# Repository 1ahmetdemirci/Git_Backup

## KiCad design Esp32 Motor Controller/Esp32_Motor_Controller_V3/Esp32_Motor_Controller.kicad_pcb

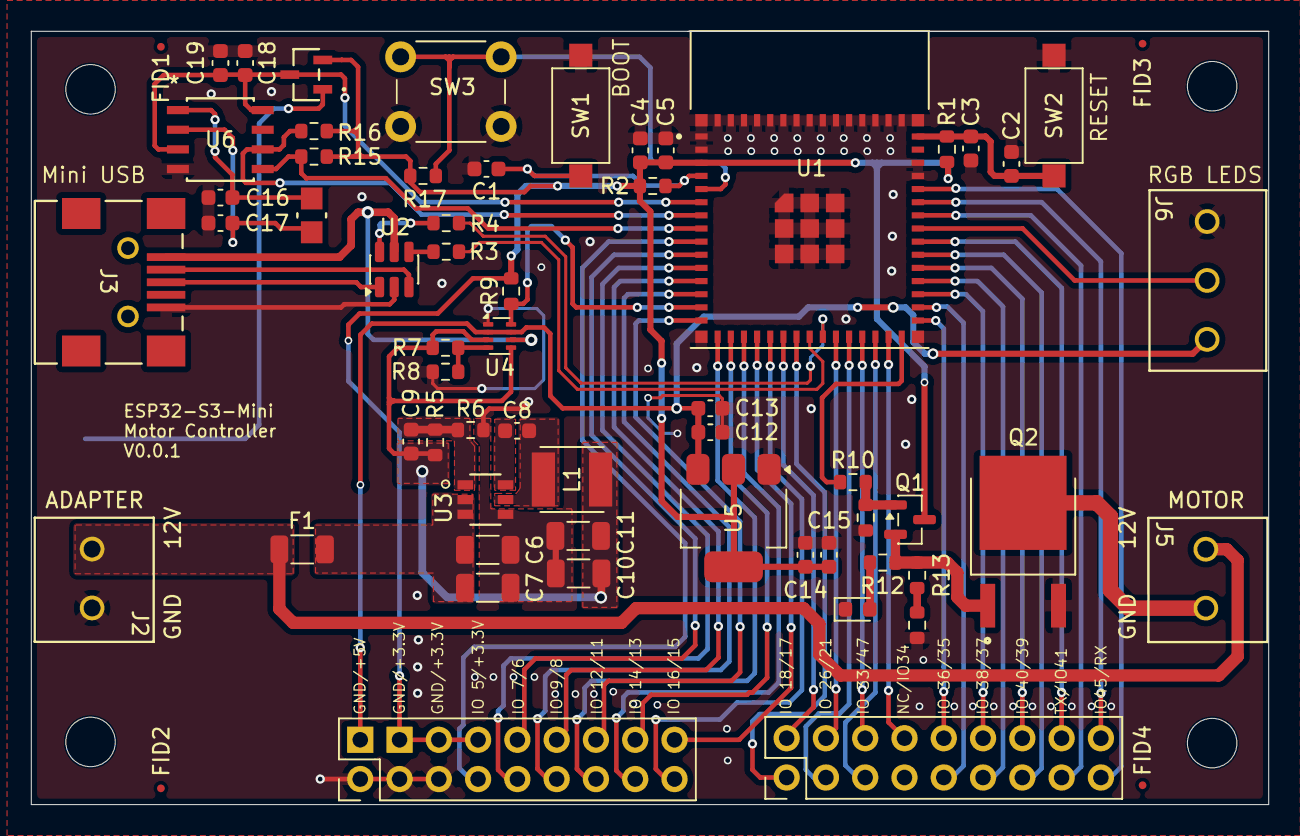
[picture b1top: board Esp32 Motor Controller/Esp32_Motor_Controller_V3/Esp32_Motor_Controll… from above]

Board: 2 copper layers, 80.0 x 50.0 mm, 63 parts (1 on the bottom side), 62 nets.

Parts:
BT2: BC2032-E2
C1, C2, C3, C4, C8, C13, C14, C18: 100nF_0603; C_0603_1608Metric
C5, C12, C15, C19: 10uF_0603; C_0603_1608Metric
C6: 10uF_1206; C_1206_3216Metric
C7: 100nF_1206; C_1206_3216Metric
C9: 47pF_0603; C_0603_1608Metric
C10, C11: 22uF_0603; C_1206_3216Metric
C16, C17: 12.5pF_0603; C_0603_1608Metric
CR1: BAT54C-TP; BAT54C-TP_MCE
D1: Green_Led; LED_0603_1608Metric
F1: C1F 2; C_1206_3216Metric
FID1, FID2, FID3, FID4: Fiducial; Fiducial_0.5mm_Mask1mm
J1, J7: Conn_02x09_Odd_Even; PinHeader_2x09_P2.54mm_Vertical
J2, J5: Screw_Terminal_01x02; 1x2_1727010
J3: USB_B_Mini; 690-005-299-043_EDA
J6: Screw_Terminal_01x03; 1x3_1727023
L1: 6.8uH; SRP4021HMCT-6R8M
Q1: MMBT2222A; SOT-23
Q2: MJD122T4G
R1, R2, R8, R9, R17: 10k_0603; R_0603_1608Metric
R3, R4: 22R_0603; R_0603_1608Metric
R5: 158k; R_0603_1608Metric
R6: 30k1; R_0603_1608Metric
R7: 33k_0603; R_0603_1608Metric
R10, R13, R15, R16: 4.7k_0603; R_0603_1608Metric
R11, R14: 47k_0603; R_0603_1608Metric
R12: 1k_0603; R_0603_1608Metric
SW1: BOOT; SW_SPST_CK_RS282G05A3
SW2: ESP_EN; SW_SPST_CK_RS282G05A3
SW3: BUTTON; SW_PUSH_6mm_H13mm
U1: ESP32-S3-MINI-1-N8
U2: USBLC6-2SC6; SOT-23-6
U3: AP63300WU-7; AP63301WU-7
U4: TPS2116DRL; SOT-583-8
U5: AMS1117-3.3; SOT-223-3_TabPin2
U6: PCF8563T/5_518; PCF8563T
XTAL1: RT3215-32.768-12.5-TR

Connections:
+3V3: C4.1, C5.1, C14.1, C15.1, CR1.2, J1.4, J1.6, J1.8, Q1.3 (C), R1.1, R2.1, R9.1, R15.1, R16.1, R17.1, U1.3 (3V3), U5.2 (VO)
+5V: C9.1, C10.1, C11.1, L1.2, R5.1, R7.2, U4.3 (VIN1), U4.5 (MODE)
+12V: F1.1, J2.1, J5.1
/ESP32_S3_Mini/ESP_D+: R4.2, U1.24 (IO20)
/ESP32_S3_Mini/ESP_D-: R3.2, U1.23 (IO19)
/ESP32_S3_Mini/LOAD: C12.1, C13.1, J1.2, J6.3, U4.2 (VOUT), U4.7 (VOUT), U5.3 (VI)
/ESP32_S3_Mini/Motor_Control: R10.1, U1.30 (IO48)
/ESP32_S3_Mini/Power Selection: R9.2, U1.14 (IO10), U4.8 (ST)
/ESP32_S3_Mini/RGB_Control: J6.2, U1.38 (IO42)
BOOT: C1.1, R2.2, SW1.2, U1.4 (IO0)
BUTTON: R17.2, SW3.2, U1.5 (IO1)
ESP_EN: C2.1, C3.2, R1.2, SW2.2, U1.45 (EN)
GND: BT2.N, C1.2, C2.2, C3.1, C4.2, C5.2, C6.2, C7.2, C10.2, C11.2, C12.2, C13.2, C14.2, C15.2, C16.2, C17.2, C18.1, C19.1, D1.1 (K), J1.1, J1.3, J1.5, J2.2, J3.5 (GND), J6.1, Q2.3, R6.2, R8.1, R11.1, R14.1, SW1.1, SW2.1, SW3.1, U1.1 (GND), U1.2 (GND), U1.42 (GND), U1.43 (GND), U1.46 (GND), U1.47 (GND), U1.48 (GND), U1.49 (GND), U1.50 (GND), U1.51 (GND), U1.52 (GND), U1.53 (GND), U1.54 (GND), U1.55 (GND), U1.56 (GND), U1.57 (GND), U1.58 (GND), U1.59 (GND), U1.60 (GND), U1.61 (GND), U1.61_1 (GND), U1.61_2 (GND), U1.61_3 (GND), U1.61_4 (GND), U1.61_5 (GND), U1.61_6 (GND), U1.61_7 (GND), U1.61_8 (GND), U1.62 (GND), U1.63 (GND), U1.64 (GND), U1.65 (GND), U2.2 (GND), U3.4 (GND), U4.1 (GND), U5.1 (GND), U6.4 (VSS)
IO5: J1.7, U1.9 (IO5)
IO6: J1.10, U1.10 (IO6)
IO7: J1.9, U1.11 (IO7)
IO8: J1.12, U1.12 (IO8)
IO9: J1.11, U1.13 (IO9)
IO11: J1.14, U1.15 (IO11)
IO12: J1.13, U1.16 (IO12)
IO13: J1.16, U1.17 (IO13)
IO14: J1.15, U1.18 (IO14)
IO15: J1.18, U1.19 (IO15)
IO16: J1.17, U1.20 (IO16)
IO17: J7.2, U1.21 (IO17)
IO18: J7.1, U1.22 (IO18)
IO21: J7.4, U1.25 (IO21)
IO26: J7.3, U1.26 (IO26)
IO33: J7.5, U1.28 (IO33)
IO34: J7.8, U1.29 (IO34)
IO35: J7.10, U1.31 (IO35)
IO36: J7.9, U1.32 (IO36)
IO37: J7.12, U1.33 (IO37)
IO38: J7.11, U1.34 (IO38)
IO39: J7.14, U1.35 (IO39)
IO40: J7.13, U1.36 (IO40)
IO41: J7.16, U1.37 (IO41)
IO45: J7.17, U1.41 (IO45)
IO47: J7.6, U1.27 (IO47)
unnamed: D1.2 (A), R12.1
unnamed: J3.3 (D+), U2.1 (I/O1)
unnamed: J3.2 (D-), U2.3 (I/O1)
unnamed: J5.2, Q2.4
unnamed: Q1.1 (B), R10.2, R11.2
unnamed: Q1.2 (E), Q2.1, R12.2, R13.2
unnamed: R13.1, R14.2
unnamed: C8.1, U3.6 (BST)
unnamed: C6.1, C7.1, F1.2, U3.2 (EN), U3.3 (VIN)
unnamed: C9.2, R5.2, R6.1, U3.1 (FB)
unnamed: C8.2, L1.1, U3.5 (SW)
unnamed: R7.1, R8.2, U4.4 (PR1)
OSC32_IN: C16.1, U6.1 (OSCI), XTAL1.1
OSC32_OUT: C17.1, U6.2 (OSCO), XTAL1.2
PWR_VBUS: J3.1 (VBUS), U2.5 (VBUS), U4.6 (VIN2)
RTC_INT: C18.2, C19.2, CR1.3, U1.6 (IO2), U6.3 (INT), U6.8 (VDD)
RTC_SCL: R16.2, U1.7 (IO3), U6.6 (SCL)
RTC_SDA: R15.2, U1.8 (IO4), U6.5 (SDA)
RXD0: J7.18, U1.40 (RXD0)
TXD0: J7.15, U1.39 (TXD0)
USB_D+: R4.1, U2.6 (I/O2)
USB_D-: R3.1, U2.4 (I/O2)
VBat_RTC: BT2.P, CR1.1

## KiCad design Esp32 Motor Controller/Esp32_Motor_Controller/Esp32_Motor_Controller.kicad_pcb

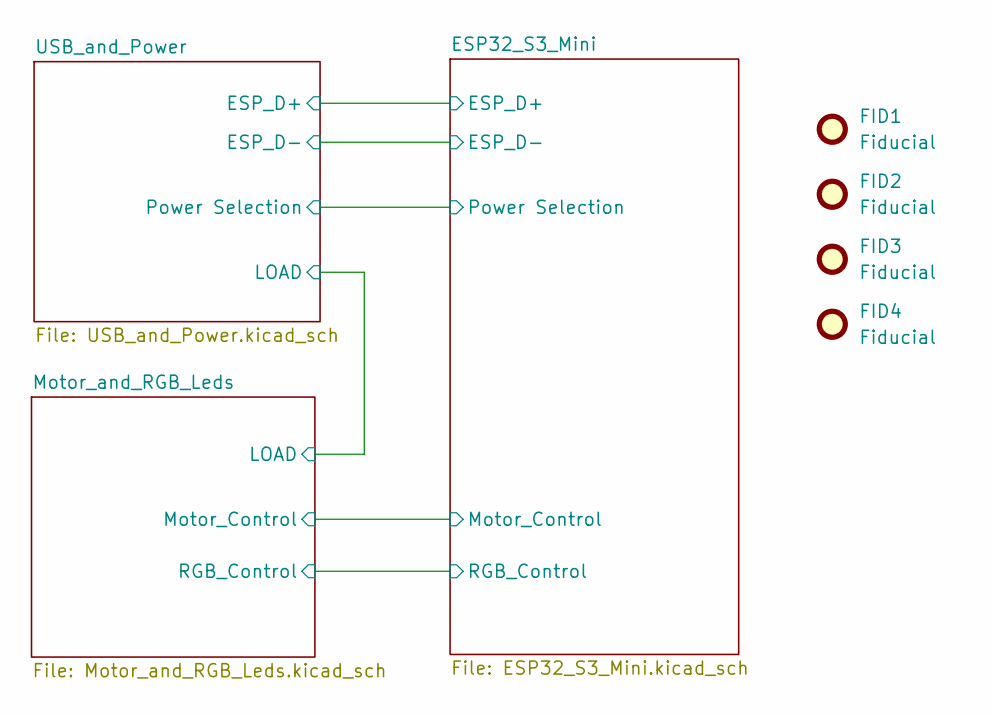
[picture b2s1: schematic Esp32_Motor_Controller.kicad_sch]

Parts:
FID1, FID2, FID3, FID4: Fiducial; Fiducial_0.5mm_Mask1mm

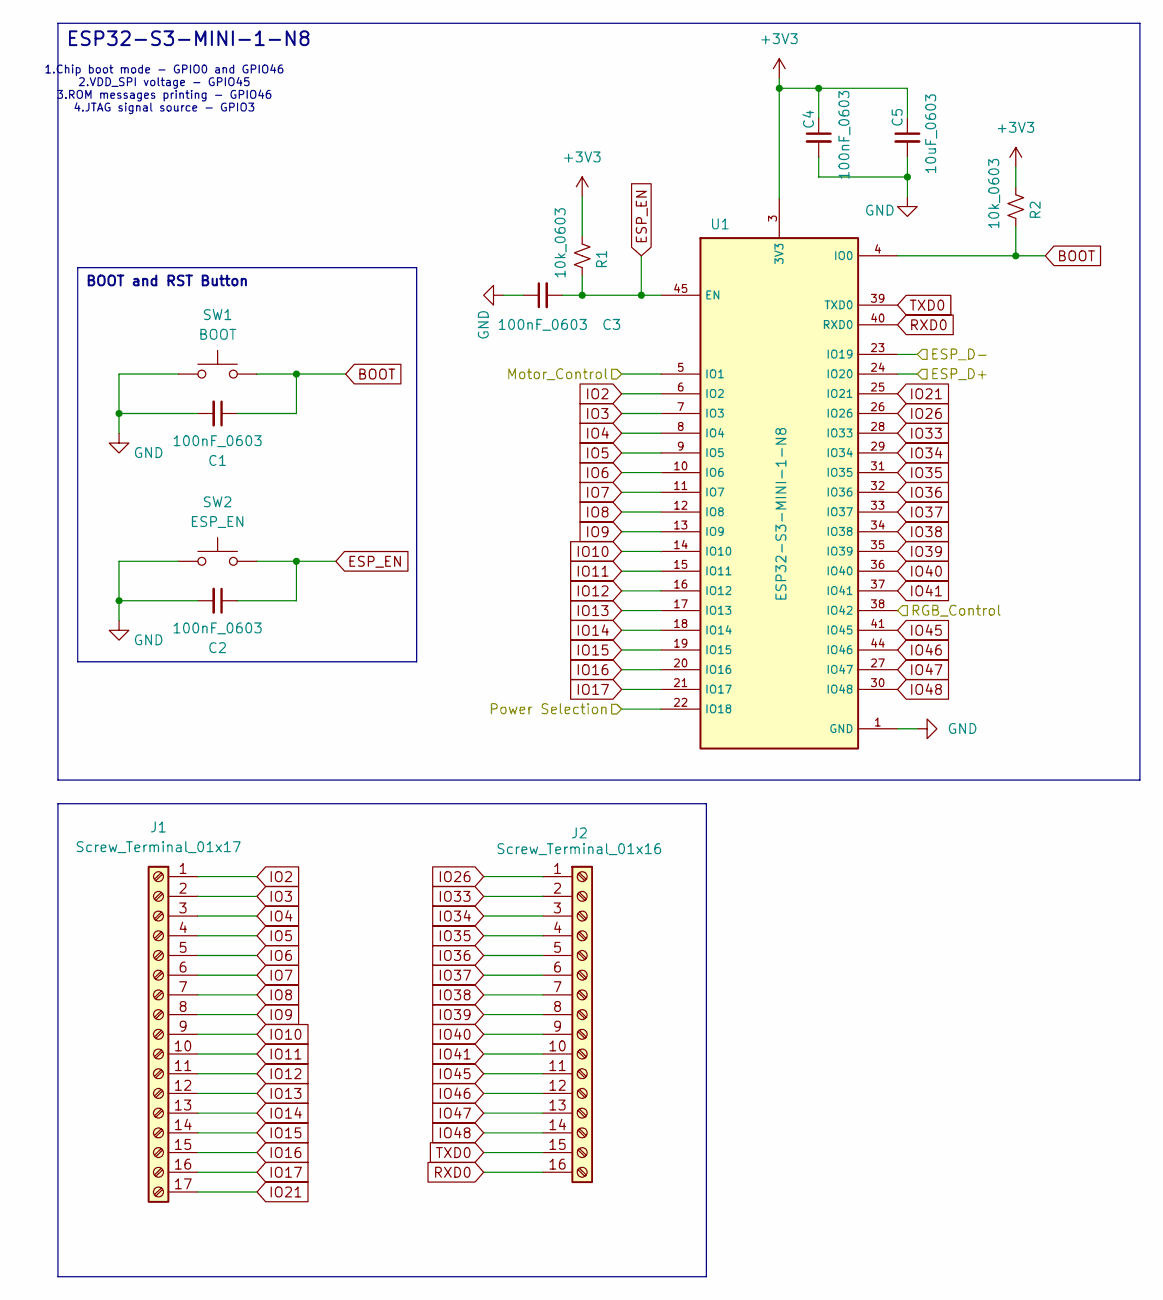
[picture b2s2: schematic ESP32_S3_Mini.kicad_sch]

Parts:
C1, C2, C3, C4: 100nF_0603; C_0603_1608Metric
C5: 10uF_0603; C_0603_1608Metric
J1: Screw_Terminal_01x17; PinHeader_1x17_P2.54mm_Vertical
J2: Screw_Terminal_01x16; PinHeader_1x16_P2.54mm_Vertical
R1, R2: 10k_0603; R_0603_1608Metric
SW1: BOOT; SW_SPST_CK_RS282G05A3
SW2: ESP_EN; SW_SPST_CK_RS282G05A3
U1: ESP32-S3-MINI-1-N8

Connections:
+3V3: C4.1, C5.1, R1.1, R2.1, U1.3 (3V3); also elsewhere on the board
/ESP32_S3_Mini/ESP_D+: U1.24 (IO20); also elsewhere on the board
/ESP32_S3_Mini/ESP_D-: U1.23 (IO19); also elsewhere on the board
/ESP32_S3_Mini/Motor_Control: U1.5 (IO1); also elsewhere on the board
/ESP32_S3_Mini/Power Selection: U1.22 (IO18); also elsewhere on the board
/ESP32_S3_Mini/RGB_Control: U1.38 (IO42); also elsewhere on the board
BOOT: C1.1, R2.2, SW1.2, U1.4 (IO0)
ESP_EN: C2.1, C3.2, R1.2, SW2.2, U1.45 (EN)
GND: C1.2, C2.2, C3.1, C4.2, C5.2, SW1.1, SW2.1, U1.1 (GND), U1.2 (GND), U1.42 (GND), U1.43 (GND), U1.46 (GND), U1.47 (GND), U1.48 (GND), U1.49 (GND), U1.50 (GND), U1.51 (GND), U1.52 (GND), U1.53 (GND), U1.54 (GND), U1.55 (GND), U1.56 (GND), U1.57 (GND), U1.58 (GND), U1.59 (GND), U1.60 (GND), U1.61 (GND), U1.61_1 (GND), U1.61_2 (GND), U1.61_3 (GND), U1.61_4 (GND), U1.61_5 (GND), U1.61_6 (GND), U1.61_7 (GND), U1.61_8 (GND), U1.62 (GND), U1.63 (GND), U1.64 (GND), U1.65 (GND); also elsewhere on the board
IO2: J1.1, U1.6 (IO2)
IO3: J1.2, U1.7 (IO3)
IO4: J1.3, U1.8 (IO4)
IO5: J1.4, U1.9 (IO5)
IO6: J1.5, U1.10 (IO6)
IO7: J1.6, U1.11 (IO7)
IO8: J1.7, U1.12 (IO8)
IO9: J1.8, U1.13 (IO9)
IO10: J1.9, U1.14 (IO10)
IO11: J1.10, U1.15 (IO11)
IO12: J1.11, U1.16 (IO12)
IO13: J1.12, U1.17 (IO13)
IO14: J1.13, U1.18 (IO14)
IO15: J1.14, U1.19 (IO15)
IO16: J1.15, U1.20 (IO16)
IO17: J1.16, U1.21 (IO17)
IO21: J1.17, U1.25 (IO21)
IO26: J2.1, U1.26 (IO26)
IO33: J2.2, U1.28 (IO33)
IO34: J2.3, U1.29 (IO34)
IO35: J2.4, U1.31 (IO35)
IO36: J2.5, U1.32 (IO36)
IO37: J2.6, U1.33 (IO37)
IO38: J2.7, U1.34 (IO38)
IO39: J2.8, U1.35 (IO39)
IO40: J2.9, U1.36 (IO40)
IO41: J2.10, U1.37 (IO41)
IO45: J2.11, U1.41 (IO45)
IO46: J2.12, U1.44 (IO46)
IO47: J2.13, U1.27 (IO47)
IO48: J2.14, U1.30 (IO48)
RXD0: J2.16, U1.40 (RXD0)
TXD0: J2.15, U1.39 (TXD0)

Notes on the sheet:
1.Chip boot mode - GPIO0 and GPIO46 2.VDD_SPI voltage - GPIO45 3.ROM messages printing - GPIO46 4.JTAG signal source - GPIO3
ESP32-S3-MINI-1-N8
BOOT and RST Button

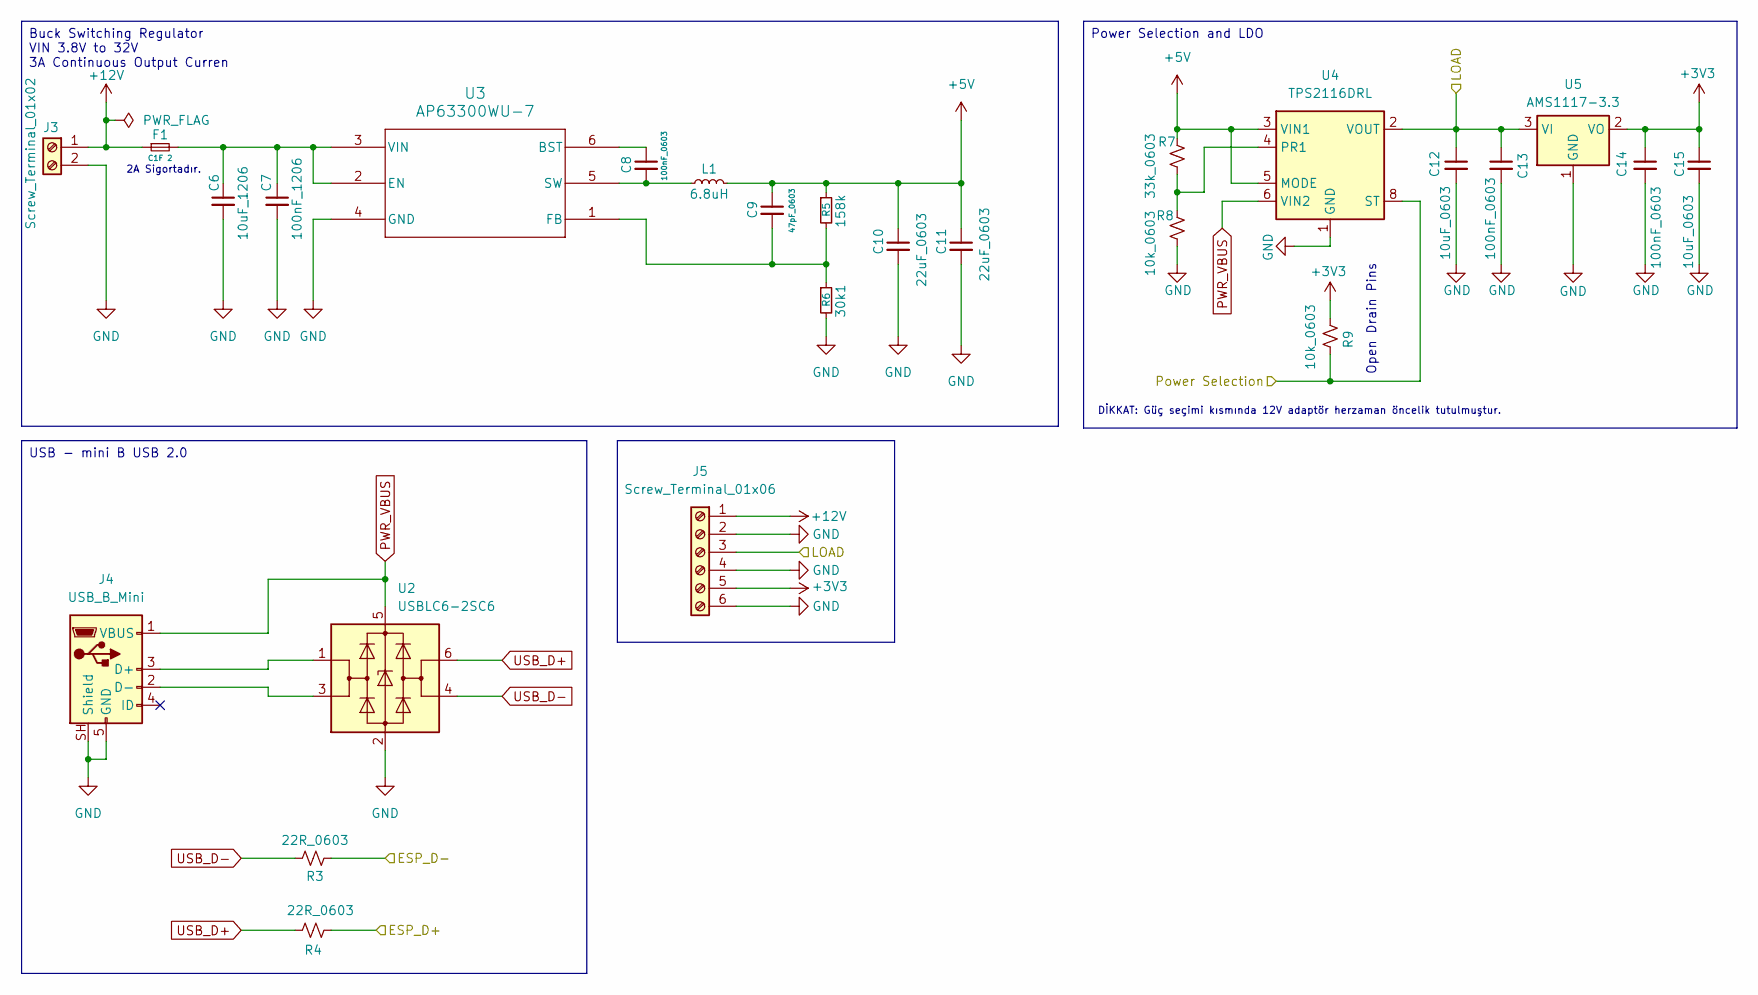
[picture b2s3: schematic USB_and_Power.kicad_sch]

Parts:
C6: 10uF_1206; C_1206_3216Metric
C7: 100nF_1206; C_1206_3216Metric
C8, C13, C14: 100nF_0603; C_0603_1608Metric
C9: 47pF_0603; C_0603_1608Metric
C10, C11: 22uF_0603; C_1206_3216Metric
C12, C15: 10uF_0603; C_0603_1608Metric
F1: C1F 2; C_1206_3216Metric
J3: Screw_Terminal_01x02; 1x2_1727010
J4: USB_B_Mini; 690-005-299-043_EDA
J5: Screw_Terminal_01x06; PinHeader_1x06_P2.54mm_Vertical
L1: 6.8uH; SRP4021HMCT-6R8M
R3, R4: 22R_0603; R_0603_1608Metric
R5: 158k; R_0603_1608Metric
R6: 30k1; R_0603_1608Metric
R7: 33k_0603; R_0603_1608Metric
R8, R9: 10k_0603; R_0603_1608Metric
U2: USBLC6-2SC6; SOT-23-6
U3: AP63300WU-7; AP63301WU-7
U4: TPS2116DRL; SOT-583-8
U5: AMS1117-3.3; SOT-223-3_TabPin2

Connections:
+3V3: C14.1, C15.1, J5.5, R9.1, U5.2 (VO); also elsewhere on the board
+5V: C9.1, C10.1, C11.1, L1.2, R5.1, R7.2, U4.3 (VIN1), U4.5 (MODE)
+12V: F1.1, J3.1, J5.1; also elsewhere on the board
/ESP32_S3_Mini/ESP_D+: R4.2; also elsewhere on the board
/ESP32_S3_Mini/ESP_D-: R3.2; also elsewhere on the board
/ESP32_S3_Mini/Power Selection: R9.2, U4.8 (ST); also elsewhere on the board
/Motor_and_RGB_Leds/LOAD: C12.1, C13.1, J5.3, U4.2 (VOUT), U4.7 (VOUT), U5.3 (VI); also elsewhere on the board
GND: C6.2, C7.2, C10.2, C11.2, C12.2, C13.2, C14.2, C15.2, J3.2, J4.5 (GND), J4.SH (Shield), J5.2, J5.4, J5.6, R6.2, R8.1, U2.2 (GND), U3.4 (GND), U4.1 (GND), U5.1 (GND); also elsewhere on the board
unnamed: J4.3 (D+), U2.1 (I/O1)
unnamed: J4.2 (D-), U2.3 (I/O1)
unnamed: C8.1, U3.6 (BST)
unnamed: C6.1, C7.1, F1.2, U3.2 (EN), U3.3 (VIN)
unnamed: C9.2, R5.2, R6.1, U3.1 (FB)
unnamed: C8.2, L1.1, U3.5 (SW)
unnamed: R7.1, R8.2, U4.4 (PR1)
PWR_VBUS: J4.1 (VBUS), U2.5 (VBUS), U4.6 (VIN2)
USB_D+: R4.1, U2.6 (I/O2)
USB_D-: R3.1, U2.4 (I/O2)

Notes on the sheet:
2A Sigortadır.
DİKKAT: Güç seçimi kısmında 12V adaptör herzaman öncelik tutulmuştur.
Open Drain Pins
USB - mini B USB 2.0
Power Selection and LDO
Buck Switching Regulator VIN 3.8V to 32V 3A Continuous Output Curren

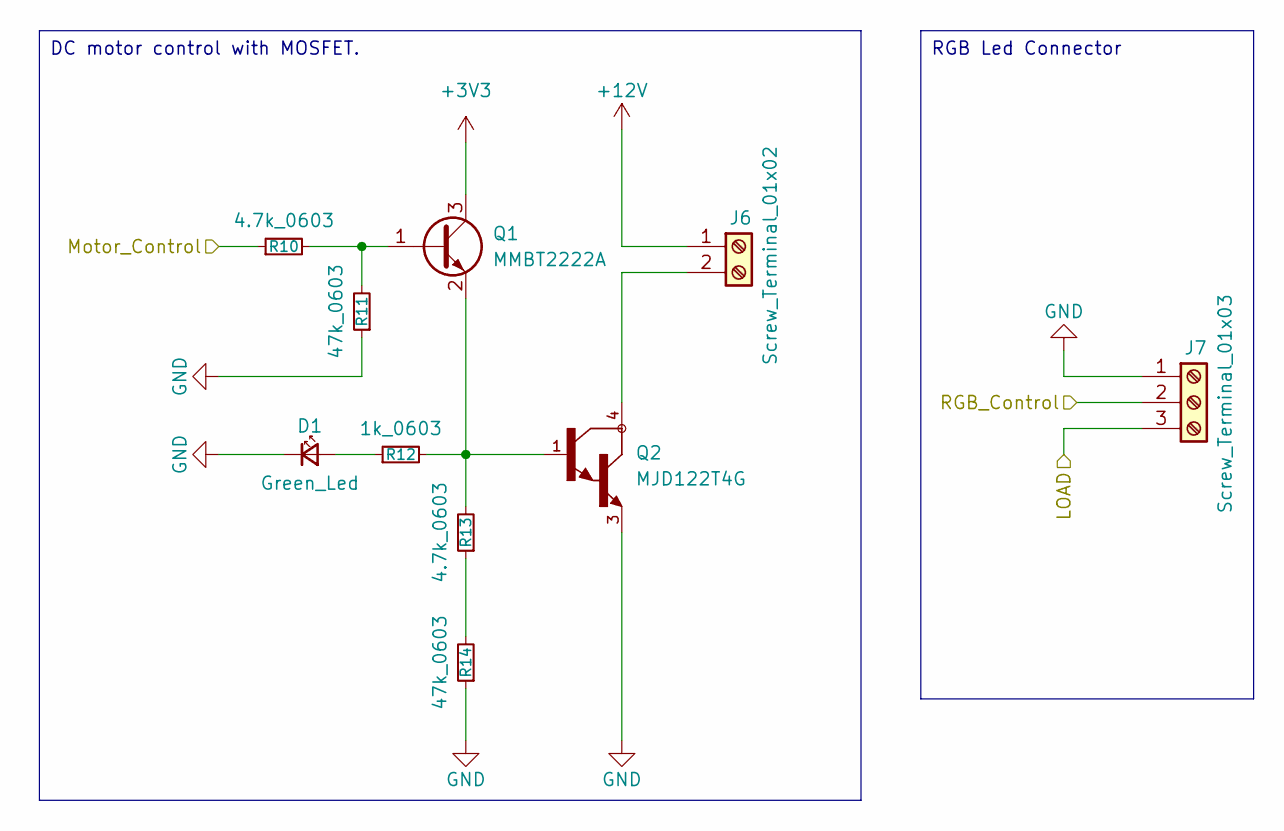
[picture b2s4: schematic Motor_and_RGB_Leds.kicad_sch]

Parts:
D1: Green_Led; LED_0603_1608Metric
J6: Screw_Terminal_01x02; 1x2_1727010
J7: Screw_Terminal_01x03; 1x3_1727023
Q1: MMBT2222A; SOT-23
Q2: MJD122T4G
R10, R13: 4.7k_0603; R_0603_1608Metric
R11, R14: 47k_0603; R_0603_1608Metric
R12: 1k_0603; R_0603_1608Metric

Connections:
+3V3: Q1.3 (C); also elsewhere on the board
+12V: J6.1; also elsewhere on the board
/ESP32_S3_Mini/Motor_Control: R10.1; also elsewhere on the board
/ESP32_S3_Mini/RGB_Control: J7.2; also elsewhere on the board
/Motor_and_RGB_Leds/LOAD: J7.3; also elsewhere on the board
GND: D1.1 (K), J7.1, Q2.3, R11.1, R14.1; also elsewhere on the board
unnamed: D1.2 (A), R12.1
unnamed: J6.2, Q2.4
unnamed: Q1.1 (B), R10.2, R11.2
unnamed: Q1.2 (E), Q2.1, R12.2, R13.2
unnamed: R13.1, R14.2

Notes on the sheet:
DC motor control with MOSFET.
RGB Led Connector

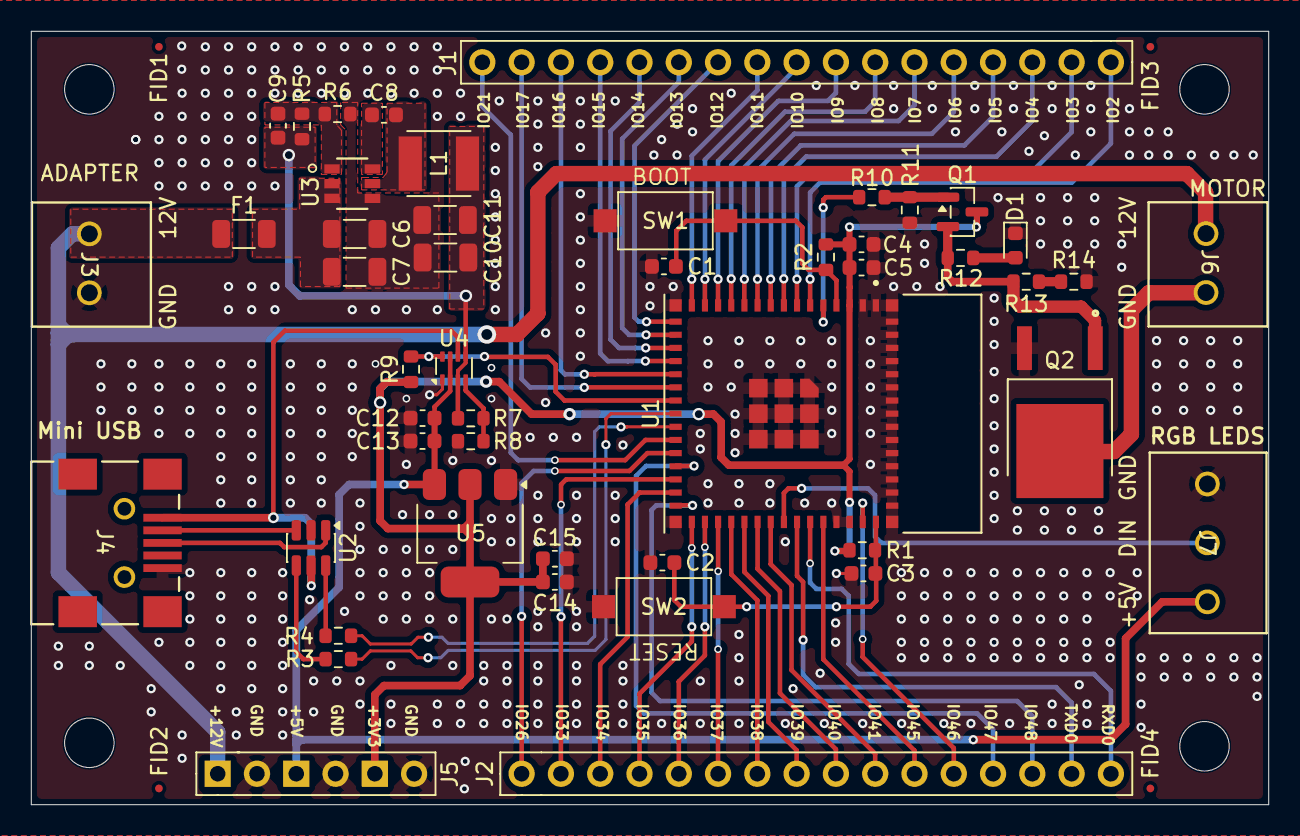
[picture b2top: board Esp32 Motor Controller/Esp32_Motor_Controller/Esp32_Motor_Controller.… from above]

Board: 2 copper layers, 80.0 x 50.0 mm, 52 parts (0 on the bottom side), 60 nets.

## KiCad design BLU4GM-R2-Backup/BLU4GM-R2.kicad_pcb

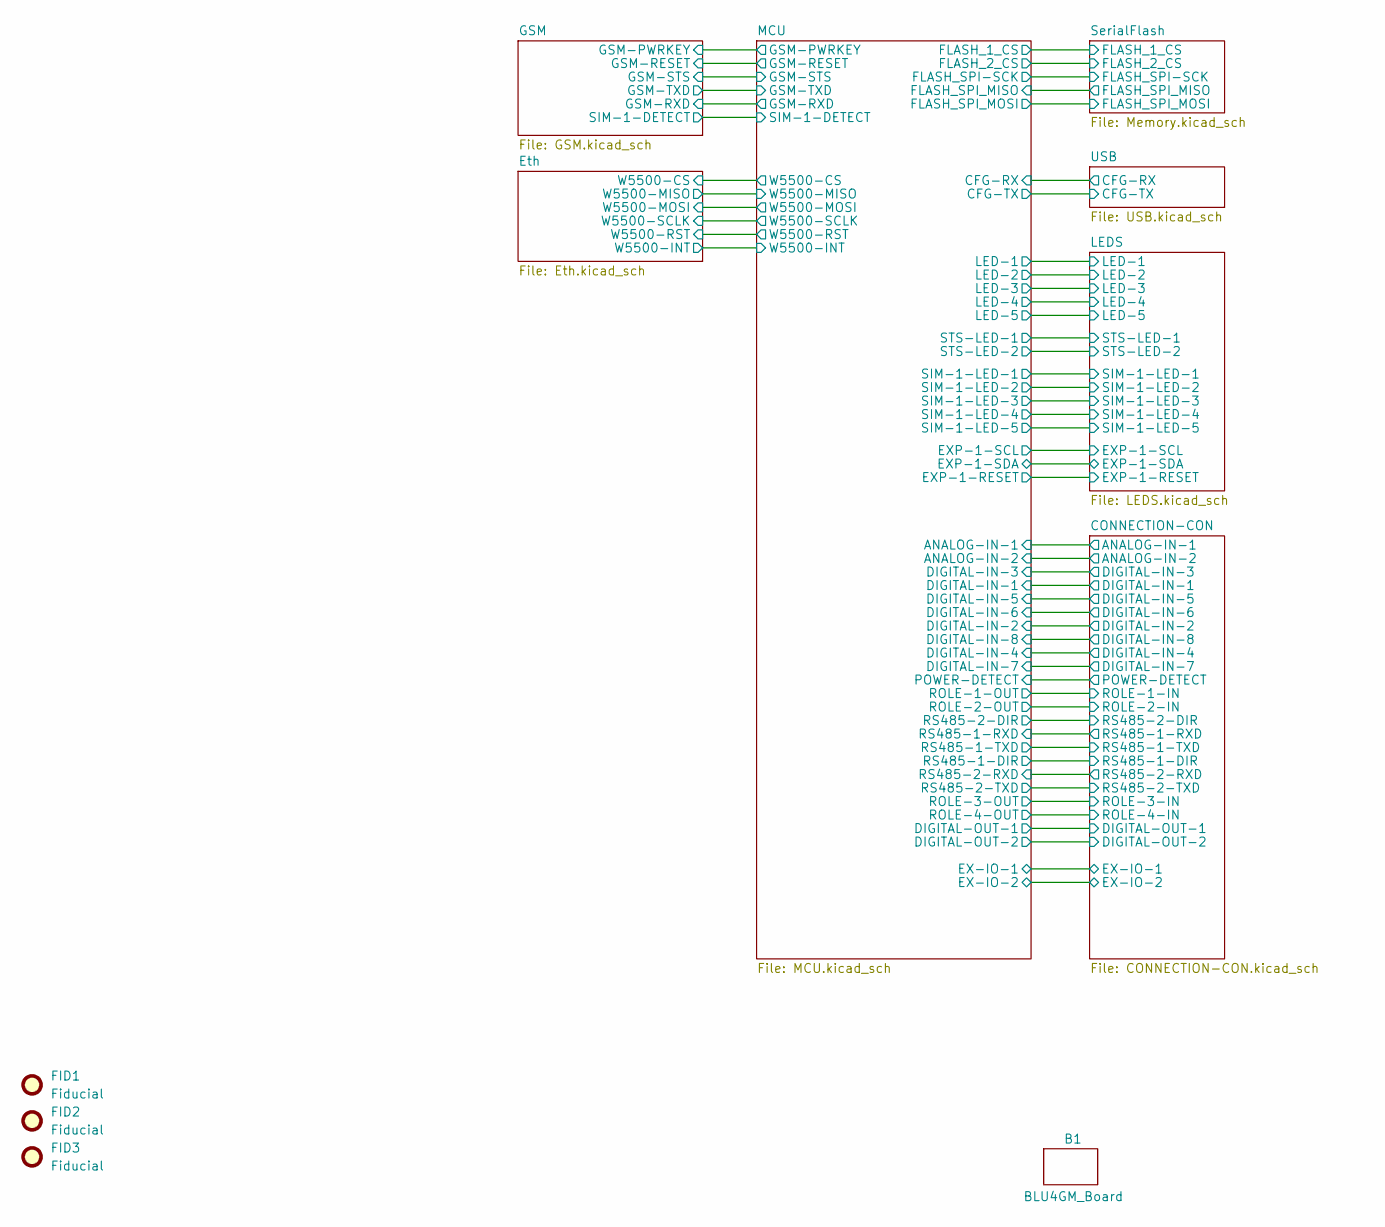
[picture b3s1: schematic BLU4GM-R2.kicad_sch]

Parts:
B1: BLU4GM_Board; BLULC-M
FID1, FID2, FID3: Fiducial; Fiducial_1mm_Mask2mm

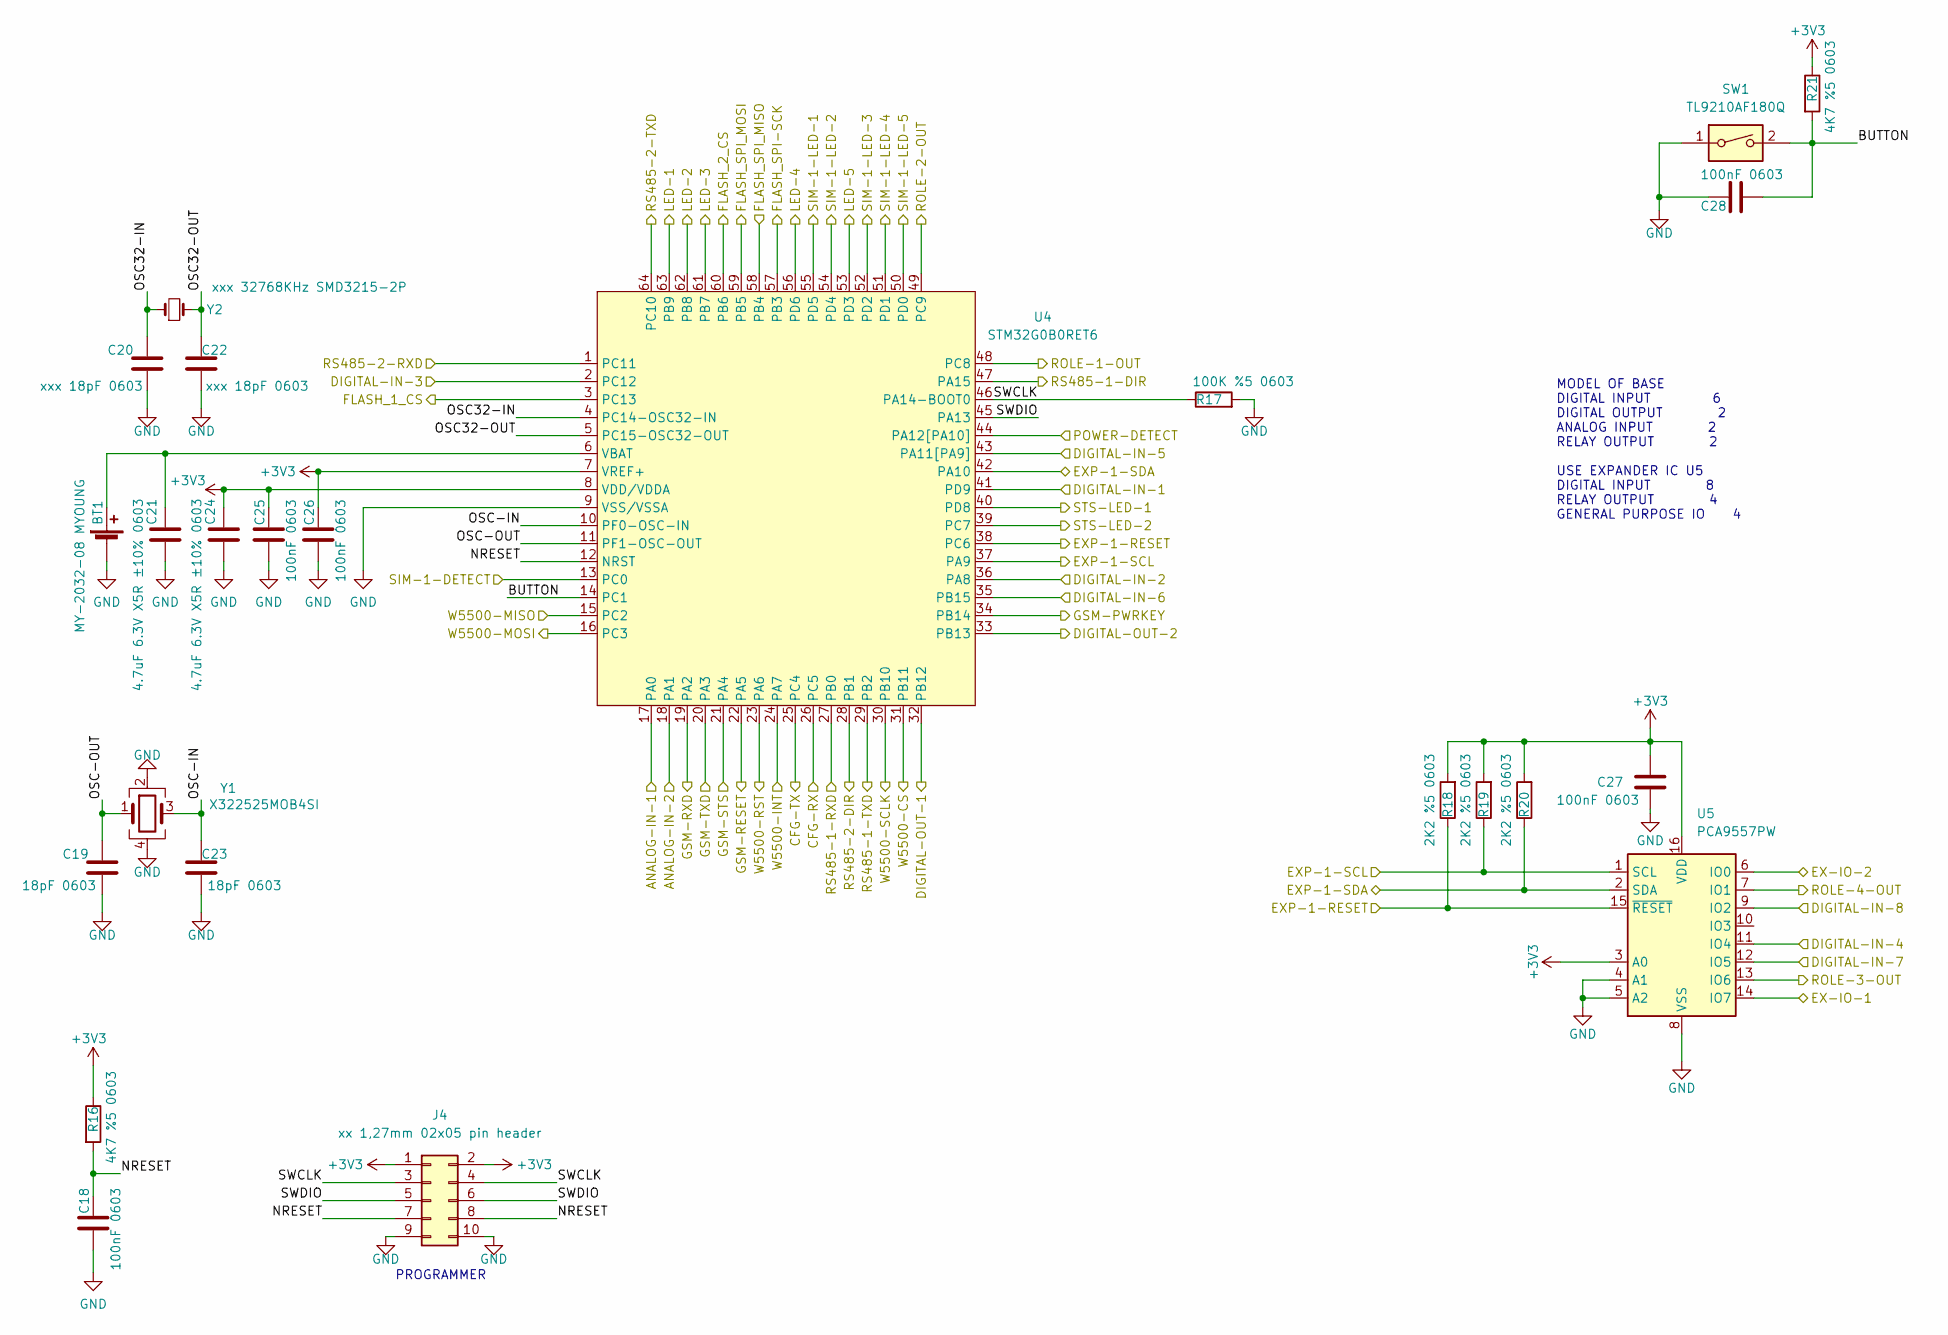
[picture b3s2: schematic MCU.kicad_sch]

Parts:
BT1: MY-2032-08 MYOUNG; MY-2032-04-R
C18, C25, C26, C27, C28: 100nF 0603; C_0603_1608Metric
C19, C23: 18pF 0603; C_0603_1608Metric
C20, C22: xxx 18pF 0603; C_0603_1608Metric
C21, C24: 4.7uF 6.3V X5R ±10% 0603; C_0603_1608Metric
J4: xx 1,27mm 02x05 pin header; PinHeader_2x05_P1.27mm_Vertical
R16, R21: 4K7 %5 0603; R_0603_1608Metric
R17: 100K %5 0603; R_0603_1608Metric
R18, R19, R20: 2K2 %5 0603; R_0603_1608Metric
SW1: TL9210AF180Q
U4: STM32G0B0RET6
U5: PCA9557PW; TSSOP-16_4.4x5mm_P0.65mm
Y1: X322525MOB4SI; Crystal_SMD_3225-4Pin_3.2x2.5mm
Y2: xxx 32768KHz SMD3215-2P; Crystal_SMD_3215-2Pin_3.2x1.5mm

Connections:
+3V3: C24.1, C25.2, C26.2, C27.1, J4.1, J4.2, R16.1, R18.2, R19.2, R20.2, R21.1, U4.7 (VREF+), U4.8 (VDD/VDDA), U5.3 (A0), U5.16 (VDD); also elsewhere on the board
/CONNECTION-CON/ANALOG-IN-1: U4.17 (PA0); also elsewhere on the board
/CONNECTION-CON/ANALOG-IN-2: U4.18 (PA1); also elsewhere on the board
/CONNECTION-CON/D-IN-1: U4.41 (PD9); also elsewhere on the board
/CONNECTION-CON/D-IN-2: U4.36 (PA8); also elsewhere on the board
/CONNECTION-CON/D-IN-3: U4.2 (PC12); also elsewhere on the board
/CONNECTION-CON/D-IN-4: U5.11 (IO4); also elsewhere on the board
/CONNECTION-CON/D-IN-5: U4.43 (PA11[PA9]); also elsewhere on the board
/CONNECTION-CON/D-IN-6: U4.35 (PB15); also elsewhere on the board
/CONNECTION-CON/D-IN-7: U5.12 (IO5); also elsewhere on the board
/CONNECTION-CON/D-IN-8: U5.9 (IO2); also elsewhere on the board
/CONNECTION-CON/DIGITAL-OUT-1: U4.32 (PB12); also elsewhere on the board
/CONNECTION-CON/DIGITAL-OUT-2: U4.33 (PB13); also elsewhere on the board
/CONNECTION-CON/EX-IO-1: U5.14 (IO7); also elsewhere on the board
/CONNECTION-CON/EX-IO-2: U5.6 (IO0); also elsewhere on the board
/CONNECTION-CON/POWER-DETECT: U4.44 (PA12[PA10]); also elsewhere on the board
/CONNECTION-CON/ROLE-1-IN: U4.48 (PC8); also elsewhere on the board
/CONNECTION-CON/ROLE-2-IN: U4.49 (PC9); also elsewhere on the board
/CONNECTION-CON/ROLE-3-IN: U5.13 (IO6); also elsewhere on the board
/CONNECTION-CON/ROLE-4-IN: U5.7 (IO1); also elsewhere on the board
/CONNECTION-CON/RS485-1-DIR: U4.47 (PA15); also elsewhere on the board
/CONNECTION-CON/RS485-1-RXD: U4.27 (PB0); also elsewhere on the board
/CONNECTION-CON/RS485-1-TXD: U4.29 (PB2); also elsewhere on the board
/CONNECTION-CON/RS485-2-DIR: U4.28 (PB1); also elsewhere on the board
/CONNECTION-CON/RS485-2-RXD: U4.1 (PC11); also elsewhere on the board
/CONNECTION-CON/RS485-2-TXD: U4.64 (PC10); also elsewhere on the board
/Eth/W5500-CS: U4.31 (PB11); also elsewhere on the board
/Eth/W5500-INT: U4.24 (PA7); also elsewhere on the board
/Eth/W5500-MISO: U4.15 (PC2); also elsewhere on the board
/Eth/W5500-MOSI: U4.16 (PC3); also elsewhere on the board
/Eth/W5500-RST: U4.23 (PA6); also elsewhere on the board
/Eth/W5500-SCLK: U4.30 (PB10); also elsewhere on the board
/GSM/GSM-PWRKEY: U4.34 (PB14); also elsewhere on the board
/GSM/GSM-RESET: U4.22 (PA5); also elsewhere on the board
/GSM/GSM-RXD: U4.19 (PA2); also elsewhere on the board
/GSM/GSM-STS: U4.21 (PA4); also elsewhere on the board
/GSM/GSM-TXD: U4.20 (PA3); also elsewhere on the board
/GSM/SIM-1-DETECT: U4.13 (PC0); also elsewhere on the board
/LEDS/EXP-1-RESET: R18.1, U4.38 (PC6), U5.15 (~RESET); also elsewhere on the board
/LEDS/EXP-1-SCL: R19.1, U4.37 (PA9), U5.1 (SCL); also elsewhere on the board
/LEDS/EXP-1-SDA: R20.1, U4.42 (PA10), U5.2 (SDA); also elsewhere on the board
/LEDS/LED-1: U4.63 (PB9); also elsewhere on the board
/LEDS/LED-2: U4.62 (PB8); also elsewhere on the board
/LEDS/LED-3: U4.61 (PB7); also elsewhere on the board
/LEDS/LED-4: U4.56 (PD6); also elsewhere on the board
/LEDS/LED-5: U4.53 (PD3); also elsewhere on the board
/LEDS/SIM-1-LED-1: U4.55 (PD5); also elsewhere on the board
/LEDS/SIM-1-LED-2: U4.54 (PD4); also elsewhere on the board
/LEDS/SIM-1-LED-3: U4.52 (PD2); also elsewhere on the board
/LEDS/SIM-1-LED-4: U4.51 (PD1); also elsewhere on the board
/LEDS/SIM-1-LED-5: U4.50 (PD0); also elsewhere on the board
/LEDS/STS-LED-1: U4.40 (PD8); also elsewhere on the board
/LEDS/STS-LED-2: U4.39 (PC7); also elsewhere on the board
/MCU/BUTTON: C28.1, R21.2, SW1.2, U4.14 (PC1)
/MCU/CFG-RX: U4.26 (PC5); also elsewhere on the board
/MCU/CFG-TX: U4.25 (PC4); also elsewhere on the board
/MCU/FLASH_1_CS: U4.3 (PC13); also elsewhere on the board
/MCU/FLASH_2_CS: U4.60 (PB6); also elsewhere on the board
/MCU/FLASH_SPI-SCK: U4.57 (PB3); also elsewhere on the board
/MCU/FLASH_SPI_MISO: U4.58 (PB4); also elsewhere on the board
/MCU/FLASH_SPI_MOSI: U4.59 (PB5); also elsewhere on the board
/MCU/NRESET: C18.2, J4.7, J4.8, R16.2, U4.12 (NRST)
/MCU/OSC32-IN: C20.1, U4.4 (PC14-OSC32-IN), Y2.1
/MCU/OSC32-OUT: C22.2, U4.5 (PC15-OSC32-OUT), Y2.2
/MCU/OSC-IN: C23.2, U4.10 (PF0-OSC-IN), Y1.3
/MCU/OSC-OUT: C19.1, U4.11 (PF1-OSC-OUT), Y1.1
/MCU/SWCLK: J4.3, J4.4, R17.1, U4.46 (PA14-BOOT0)
/MCU/SWDIO: J4.5, J4.6, U4.45 (PA13)
GND: BT1.2 (-), C18.1, C19.2, C20.2, C21.2, C22.1, C23.1, C24.2, C25.1, C26.1, C27.2, C28.2, J4.9, J4.10, R17.2, SW1.1, U4.9 (VSS/VSSA), U5.4 (A1), U5.5 (A2), U5.8 (VSS), Y1.2, Y1.4; also elsewhere on the board
unnamed: BT1.1 (+), C21.1, U4.6 (VBAT)

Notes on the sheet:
PROGRAMMER
MODEL OF BASE DIGITAL INPUT 6 DIGITAL OUTPUT 2 ANALOG INPUT 2 RELAY OUTPUT 2 USE EXPANDER IC U5 DIGITAL INPUT 8 RELAY OUTPUT 4 GENERAL PURPOSE IO 4

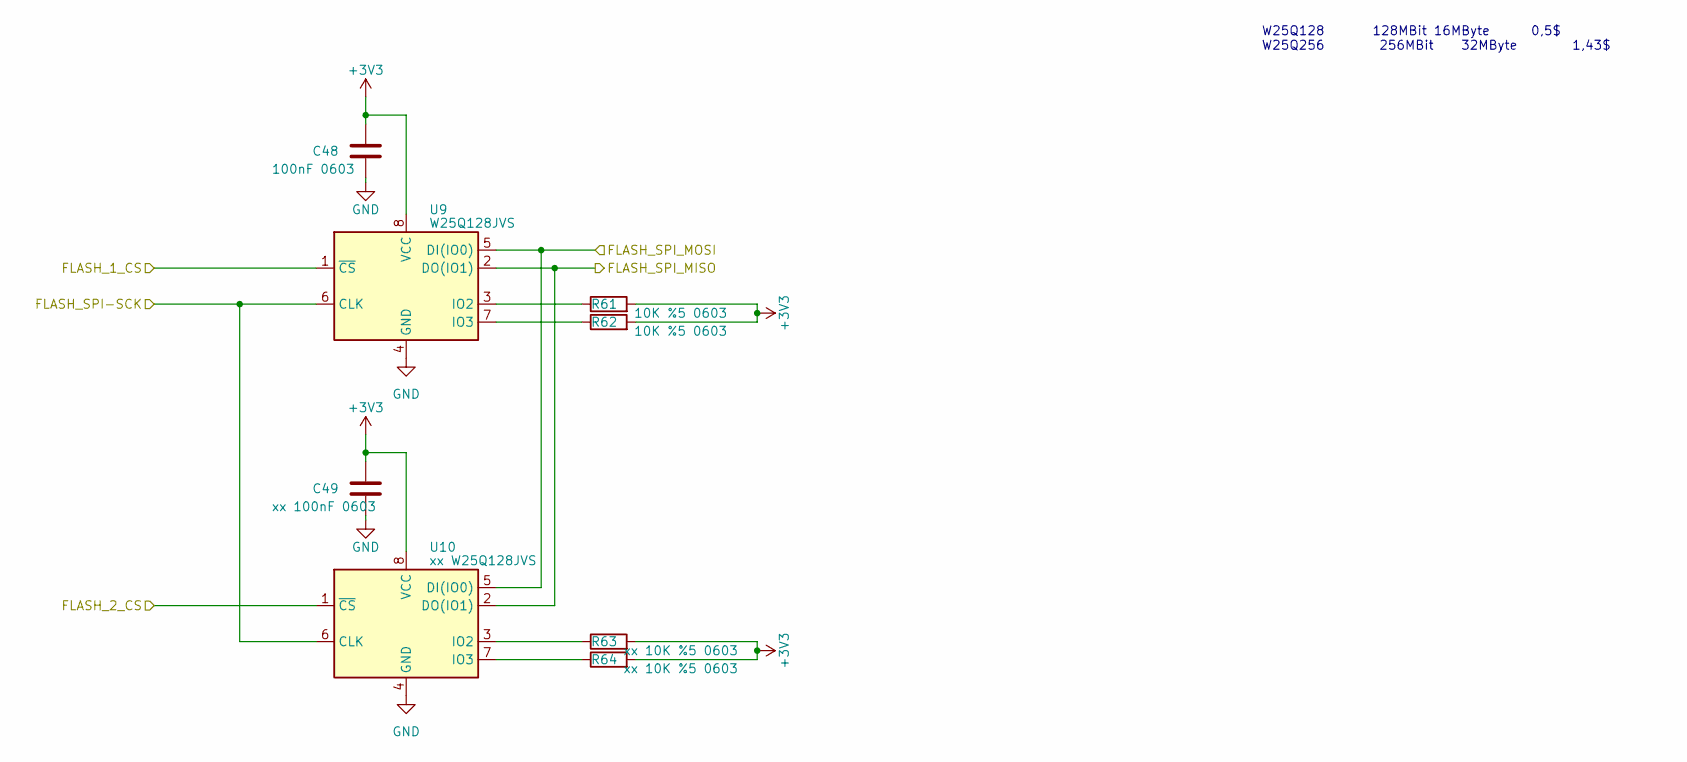
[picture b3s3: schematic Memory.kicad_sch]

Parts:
C48: 100nF 0603; C_0603_1608Metric
C49: xx 100nF 0603; C_0603_1608Metric
R61, R62: 10K %5 0603; R_0603_1608Metric
R63, R64: xx 10K %5 0603; R_0603_1608Metric
U9: W25Q128JVS; SOIC-8_5.23x5.23mm_P1.27mm
U10: xx W25Q128JVS; SOIC-8_5.23x5.23mm_P1.27mm

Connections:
+3V3: C48.1, C49.1, R61.2, R62.2, R63.2, R64.2, U9.8 (VCC), U10.8 (VCC); also elsewhere on the board
/MCU/FLASH_1_CS: U9.1 (~CS); also elsewhere on the board
/MCU/FLASH_2_CS: U10.1 (~CS); also elsewhere on the board
/MCU/FLASH_SPI-SCK: U9.6 (CLK), U10.6 (CLK); also elsewhere on the board
/MCU/FLASH_SPI_MISO: U9.2 (DO(IO1)), U10.2 (DO(IO1)); also elsewhere on the board
/MCU/FLASH_SPI_MOSI: U9.5 (DI(IO0)), U10.5 (DI(IO0)); also elsewhere on the board
GND: C48.2, C49.2, U9.4 (GND), U10.4 (GND); also elsewhere on the board
unnamed: R61.1, U9.3 (IO2)
unnamed: R62.1, U9.7 (IO3)
unnamed: R63.1, U10.3 (IO2)
unnamed: R64.1, U10.7 (IO3)

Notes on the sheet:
W25Q128 128MBit 16MByte 0,5$ W25Q256 256MBit 32MByte 1,43$
